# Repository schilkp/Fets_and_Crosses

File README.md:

# Fets and Crosses
### Philipp Schilk

An implementation of the classic Tic-Tac-Toe / Knots and Crosses game
built entirely from 2458 discrete transistors.

Why? *Because.*

## Features
- Players vs Player and Player vs Computer with engine fully implemented in transistors.
- Win-State and End-State detection
- Enforces game rules (prevents illegal moves)
- Shiny LEDs

## Release & Schematic viewing
See [Github releases](https://wwww.github.com/TheSchilk/Fets_and_Crosses/releases/) for all production files, schematics, etc...

Although the schematic is included in PDF form, it is recommended to view the schematic in KiCad directly.

## Implementation Details

All logic implemented in standard CMOS logic using discrete transistors.

The engine opponent is also implemented in logic on a seperate PCB, but can be substituted
with a ROM IC on the main IC.

JP1 has to be added when using the ROM IC, and removed when using the engine PCB.

## Overview

**Logisim:**  
	Logic Simulation.
	Download LogiSim at [cburch.com](http://www.cburch.com/logisim/).  
	
**Scripts:**  
	Various python scripts to test different engine designs and generate ROM contents.  

**ROM:**  
	Generated ROM files.  
	
**ECAD:**  
    All KiCad projects and production files.  
    
## Other Links
[Construction Timelapse](https://www.youtube.com/watch?v=Lz2p190qZ2Q)

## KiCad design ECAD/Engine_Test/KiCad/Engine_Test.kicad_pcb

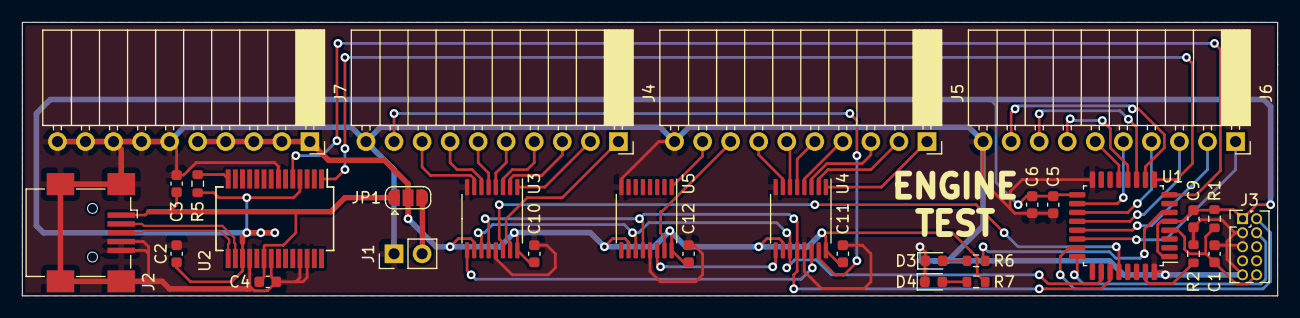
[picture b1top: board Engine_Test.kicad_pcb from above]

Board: 2 copper layers, 113.7 x 24.8 mm, 30 parts (0 on the bottom side), 49 nets.

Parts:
C1, C2, C3, C4, C9, C10, C11, C12: 0u1; C_0603_1608Metric
C5: 10n; C_0603_1608Metric
C6: 1u; C_0603_1608Metric
D3: LED; LED_0603_1608Metric
D4: PWR LED; LED_0603_1608Metric
J1: 5V_in; PinHeader_1x02_P2.54mm_Vertical
J2: USB_B_Micro; USB_Mini-B_Wuerth_65100516121_Horizontal
J3: ARM_SWD; PinHeader_2x05_P1.27mm_Vertical
J4: P1; PinSocket_1x10_P2.54mm_Horizontal
J5: P2; PinSocket_1x10_P2.54mm_Horizontal
J6: MOVE; PinSocket_1x10_P2.54mm_Horizontal
J7: PWR; PinSocket_1x10_P2.54mm_Horizontal
JP1: 5V Select; SolderJumper-3_P1.3mm_Open_RoundedPad1.0x1.5mm
R1, R2, R5: 10K; R_0603_1608Metric
R6, R7: rled; R_0603_1608Metric
U1: STM32F030K6Tx; LQFP-32_7x7mm_P0.8mm
U2: FT232RL; SSOP-28_5.3x10.2mm_P0.65mm
U3, U4, U5: 74HCT595PW; TSSOP-16_4.4x5mm_P0.65mm

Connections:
+3V3: C2.1, C5.1, C6.1, C9.1, J3.1, R1.1, R5.1, U1.1, U1.5, U1.17, U2.4, U2.17
+5V: C10.1, C11.1, C12.1, J7.1, J7.2, J7.3, J7.4, J7.5, JP1.2, R7.1, U3.10, U3.16, U4.10, U4.16, U5.10, U5.16
/CLK: J3.4, U1.24
/D+: J2.3, U2.15
/D-: J2.2, U2.16
/DIO: J3.2, U1.23
/ENGINE_OUT_0: J6.9, U1.10
/ENGINE_OUT_1: J6.8, U1.11
/ENGINE_OUT_2: J6.7, U1.12
/ENGINE_OUT_3: J6.6, U1.13
/ENGINE_OUT_4: J6.5, U1.18
/ENGINE_OUT_5: J6.4, U1.19
/ENGINE_OUT_6: J6.3, U1.20
/ENGINE_OUT_7: J6.2, U1.21
/ENGINE_OUT_8: J6.1, U1.22
/LED1: R6.1, U1.6
/OUT_CLK: U1.26, U3.11, U4.11, U5.11
/OUT_DATA: U1.28, U3.14
/OUT_LATCH: U1.27, U3.12, U4.12, U5.12
/UART_MCU_RX: U1.9, U2.1
/UART_MCU_TX: U1.8, U2.5
/V_USB: C3.1, C4.1, J2.1, JP1.1, U2.20
/nRST: C1.1, J3.10, R1.2, U1.4
GND: C1.2, C2.2, C3.2, C4.2, C5.2, C6.2, C9.2, C10.2, C11.2, C12.2, D3.1, D4.1, J1.1, J2.4, J2.5, J2.6, J3.3, J3.5, J3.9, J4.10, J5.10, J6.10, J7.6, J7.7, J7.8, J7.9, J7.10, R2.2, U1.16, U1.32, U2.7, U2.18, U2.21, U2.25, U2.26, U3.8, U3.13, U4.8, U4.13, U5.8, U5.13
unnamed: D3.2, R6.2
unnamed: D4.2, R7.2
unnamed: J1.2, JP1.3
unnamed: J4.1, U3.15
unnamed: J4.2, U3.1
unnamed: J4.3, U3.2
unnamed: J4.4, U3.3
unnamed: J4.5, U3.4
unnamed: J4.6, U3.5
unnamed: J4.7, U3.6
unnamed: J4.8, U3.7
unnamed: J4.9, U4.15
unnamed: J5.1, U4.1
unnamed: J5.2, U4.2
unnamed: J5.3, U4.3
unnamed: J5.4, U4.4
unnamed: J5.5, U4.5
unnamed: J5.6, U4.6
unnamed: J5.7, U4.7
unnamed: J5.8, U5.15
unnamed: J5.9, U5.1
unnamed: R2.1, U1.31
unnamed: R5.2, U2.14
unnamed: U3.9, U4.14
unnamed: U4.9, U5.14
